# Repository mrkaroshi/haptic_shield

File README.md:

This hardware and software is provided under the MIT License.

Haptic Shield Firmware cheatsheet:

'd' - debug mode, will print out all changes

'eX' - enable a driver, X is the number and they go in order left to right of '8, 4, 2, 1, 128, 64, 32, 16' (don't ask why)

'p' - puts selected driver into playback mode, and it will accept values of voltage level

'rX' - sets the voltage level of a driver output, 128 being the midpoint (highest)

'iX' - puts the selected driver into trigger mode, X is the number code for the waveform you want to set (see the datasheet). If you don't set X it will default to either 16 or the last used.

't' - triggers the enabled driver provided it has been selected with 'eX'

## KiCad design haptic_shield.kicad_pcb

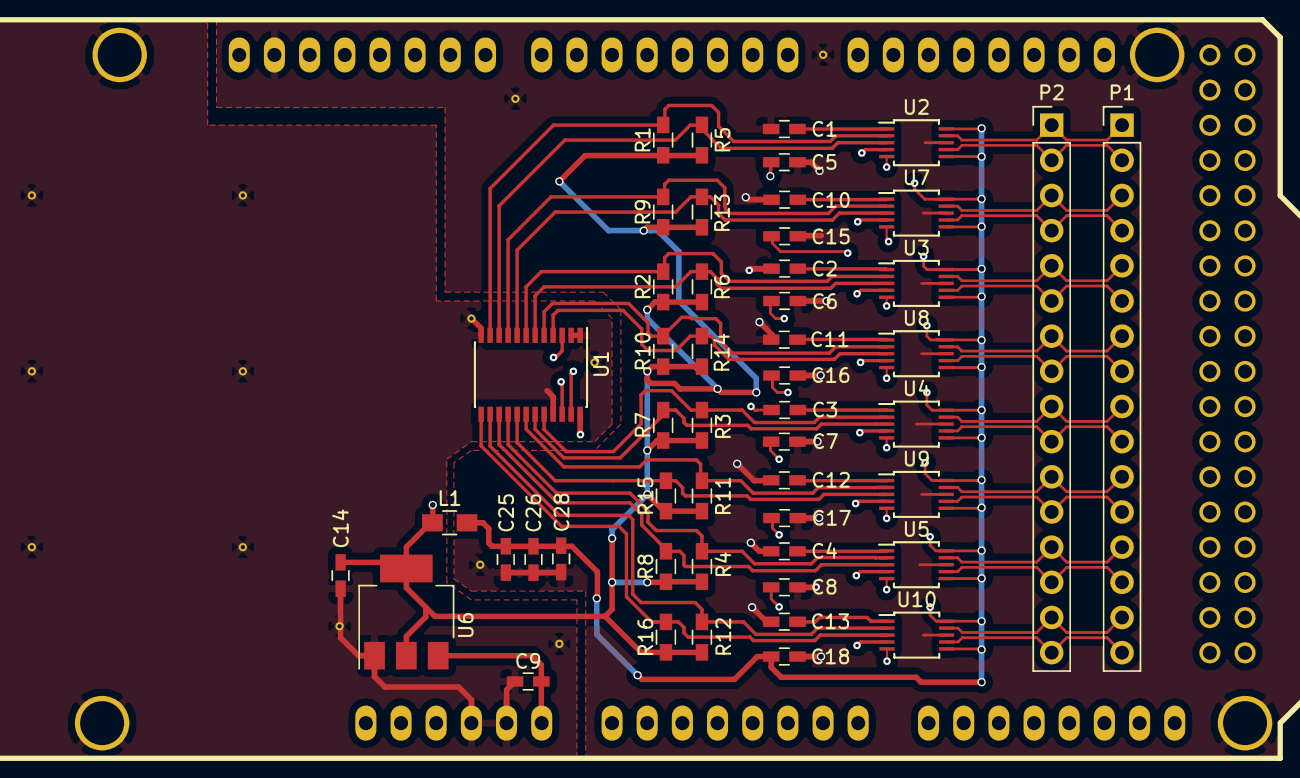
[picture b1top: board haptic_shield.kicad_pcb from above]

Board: 4 copper layers, 64 parts (0 on the bottom side), 64 nets.

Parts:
C1, C2, C3, C4, C10, C11, C12, C13: 1uF; C_0603_HandSoldering
C5, C6, C7, C8, C15, C16, C17, C18, C28: 0.1uF; C_0603_HandSoldering
C9: 10uF; C_0603_HandSoldering
C14, C25: 22uF; C_0603_HandSoldering
C26: 0.01uF; C_0603_HandSoldering
L1: 5 Ohm; C_0805_HandSoldering
P1, P2: CONN_01X16; Pin_Header_Straight_1x16_Pitch2.54mm
R1, R2, R3, R4, R5, R6, R7, R8, R9, R10, R11, R12, R13, R14, R15, R16: 2k2; R_0603_HandSoldering
SHIELD1: ARDUINO_MEGA_SHIELD; ARDUINO_MEGA_SHIELD_040pins
U1: TCA9548A; TSSOP-24_4.4x7.8mm_Pitch0.65mm
U2, U3, U4, U5, U7, U8, U9, U10: DRV2605L; TSSOP-10_3x3mm_Pitch0.5mm
U6: AP111750; SOT-223
V: VIA-0.6mm
V#2, V#3, V#4, V#5, V#6, V#7, V#8, V#9, V#10, V#11, V#12, V#13: VIA-0.6mm

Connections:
+5V: C14.1, L1.1, R1.1, R2.1, R3.1, R4.1, R5.1, R6.1, R7.1, R8.1, R9.1, R10.1, R11.1, R12.1, R13.1, R14.1, R15.1, R16.1, U1.24, U6.2, U6.4
+5VA: C5.1, C6.1, C7.1, C8.1, C15.1, C16.1, C17.1, C18.1, C25.1, C26.1, C28.1, L1.2, U2.6, U2.10, U3.6, U3.10, U4.6, U4.10, U5.6, U5.10, U7.6, U7.10, U8.6, U8.10, U9.6, U9.10, U10.6, U10.10
+12V: C9.1, SHIELD1.V_IN, U6.3
ANA1: SHIELD1.2, U2.4
ANA2: SHIELD1.3, U7.4
ANA3: SHIELD1.4, U3.4
ANA4: SHIELD1.5, U8.4
ANA5: SHIELD1.6, U4.4
ANA6: SHIELD1.7, U9.4
ANA7: SHIELD1.8, U5.4
ANA8: SHIELD1.9, U10.4
EN1: SHIELD1.24, U2.5
EN2: SHIELD1.28, U7.5
EN3: SHIELD1.32, U3.5
EN4: SHIELD1.36, U8.5
EN5: SHIELD1.40, U4.5
EN6: SHIELD1.44, U9.5
EN7: SHIELD1.46, U5.5
EN8: SHIELD1.48, U10.5
GNDA: C1.1, C2.1, C3.1, C4.1, C5.2, C6.2, C7.2, C8.2, C10.1, C11.1, C12.1, C13.1, C15.2, C16.2, C17.2, C18.2, C25.2, C26.2, C28.2, SHIELD1.GND1, SHIELD1.GND3, U2.8, U3.8, U4.8, U5.8, U7.8, U8.8, U9.8, U10.8, V#7.1, V#10.1, V#13.1
GNDD: C9.2, C14.2, SHIELD1.GND1, SHIELD1.GND2, SHIELD1.GND4, SHIELD1.GND5, U1.1, U1.2, U1.12, U1.21, U6.1, V.1, V#2.1, V#3.1, V#4.1, V#5.1, V#6.1, V#8.1, V#9.1, V#11.1, V#12.1
MOT1+: P1.2, P2.2, U2.7
MOT1-: P1.1, P2.1, U2.9
MOT2+: P1.4, P2.4, U7.7
MOT2-: P1.3, P2.3, U7.9
MOT3+: P1.6, P2.6, U3.7
MOT3-: P1.5, P2.5, U3.9
MOT4+: P1.8, P2.8, U8.7
MOT4-: P1.7, P2.7, U8.9
MOT5+: P1.10, P2.10, U4.7
MOT5-: P1.9, P2.9, U4.9
MOT6+: P1.12, P2.12, U9.7
MOT6-: P1.11, P2.11, U9.9
MOT7+: P1.14, P2.14, U5.7
MOT7-: P1.13, P2.13, U5.9
MOT8+: P1.16, P2.16, U10.7
MOT8-: P1.15, P2.15, U10.9
unnamed: C1.2, U2.1
unnamed: C2.2, U3.1
unnamed: C3.2, U4.1
unnamed: C4.2, U5.1
unnamed: C10.2, U7.1
unnamed: C11.2, U8.1
unnamed: C12.2, U9.1
unnamed: C13.2, U10.1
RST: SHIELD1.RST, U1.3
SC0: R1.2, U1.11, U2.2
SC1: R9.2, U1.9, U7.2
SC2: R2.2, U1.7, U3.2
SC3: R10.2, U1.5, U8.2
SC4: R3.2, U1.20, U4.2
SC5: R11.2, U1.18, U9.2
SC6: R4.2, U1.16, U5.2
SC7: R12.2, U1.14, U10.2
SCL_MASTER: SHIELD1.21, U1.22
SD0: R5.2, U1.10, U2.3
SD1: R13.2, U1.8, U7.3
SD2: R6.2, U1.6, U3.3
SD3: R14.2, U1.4, U8.3
SD4: R7.2, U1.19, U4.3
SD5: R15.2, U1.17, U9.3
SD6: R8.2, U1.15, U5.3
SD7: R16.2, U1.13, U10.3
SDA_MASTER: SHIELD1.20, U1.23

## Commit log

2018-01-15 Rewritten a series of commands from the Adafruit library for the TCA9548A and DRV2605L to comply with shield operation.
2018-01-15 Added most of the primary functions, ready for first test.
2018-01-19 Complete rewrite after getting the first features working.
2018-01-23 Implemented basic functionality (messy) of enabling a DRV via serial, triggering one, setting RTP mode and INTTRIG mode.
2018-01-23 Added debug toggle for serial output during use in a bid to speed up reactivity. Triggering is still sluggish.
2018-01-23 Optimising the Haptic Shield main loop, aiming for sub 350 uS.
2018-01-25 Solved the latency issue - serialread was reading into a much larger array than necessary. Serial commands have to be sent with a Line End and Carriage Return to keep speed high also.
2018-01-25 Bug fix for sending back-to-back commands e.g. 'r128\n\c\' 'r1\n\c\' and getting the motor driver to respond in real time, untested.
2018-01-26 Broken code wherein the final argument of the 'waveform trigger' is not taken successfully when two commands are put on the same serial string - results in ignored information on the second command.
2018-01-29 Fixed a bug where serial port would wait for timeout on sending single byte. Serial comms took 1s to send a single char, but 320uS to transmit two. Timeout manually set to 2ms, setting it to 1ms cras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
2018-02-19 Full fabrication list and all project files for KiCad
